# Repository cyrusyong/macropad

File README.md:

# macropad
Custom Macropad consisting of four keys

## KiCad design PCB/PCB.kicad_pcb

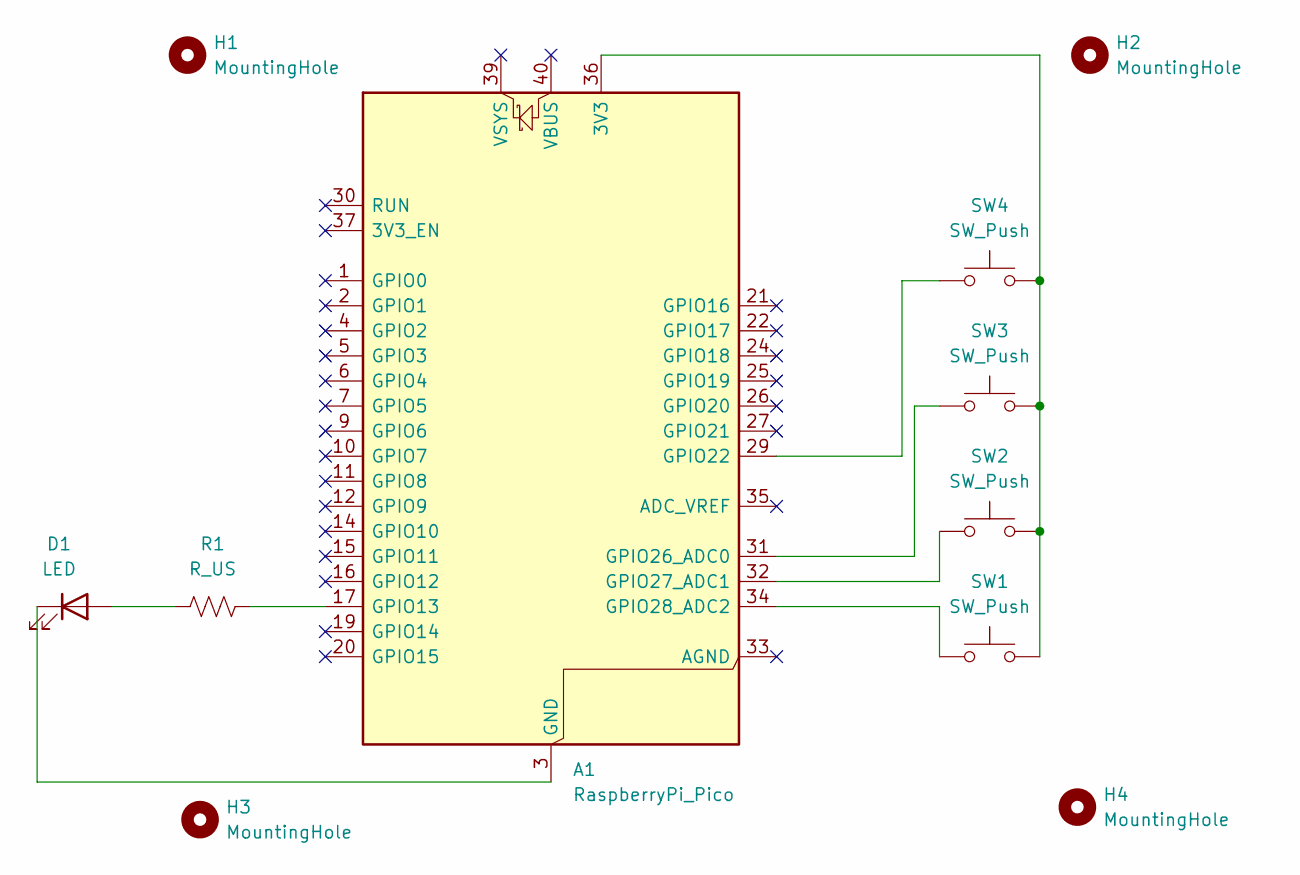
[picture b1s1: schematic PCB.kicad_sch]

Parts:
A1: RaspberryPi_Pico; RaspberryPi_Pico_Common_Unspecified
D1: LED; LED_1210_3225Metric_Pad1.42x2.65mm_HandSolder
H1, H2, H3, H4: MountingHole; MountingHole_2.2mm_M2
R1: R_US; R_0805_2012Metric_Pad1.20x1.40mm_HandSolder
SW1, SW2, SW3, SW4: SW_Push; SW_Cherry_MX_1.00u_PCB

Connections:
unnamed: A1.36 (3V3), SW1.2, SW2.2, SW3.2, SW4.2
unnamed: A1.17 (GPIO13), R1.2
unnamed: A1.29 (GPIO22), SW4.1
unnamed: A1.31 (GPIO26_ADC0), SW3.1
unnamed: A1.32 (GPIO27_ADC1), SW2.1
unnamed: A1.34 (GPIO28_ADC2), SW1.1
unnamed: D1.2 (A), R1.1
unnamed: A1.3 (GND), A1.8 (GND), A1.13 (GND), A1.18 (GND), A1.23 (GND), A1.28 (GND), A1.38 (GND), D1.1 (K)

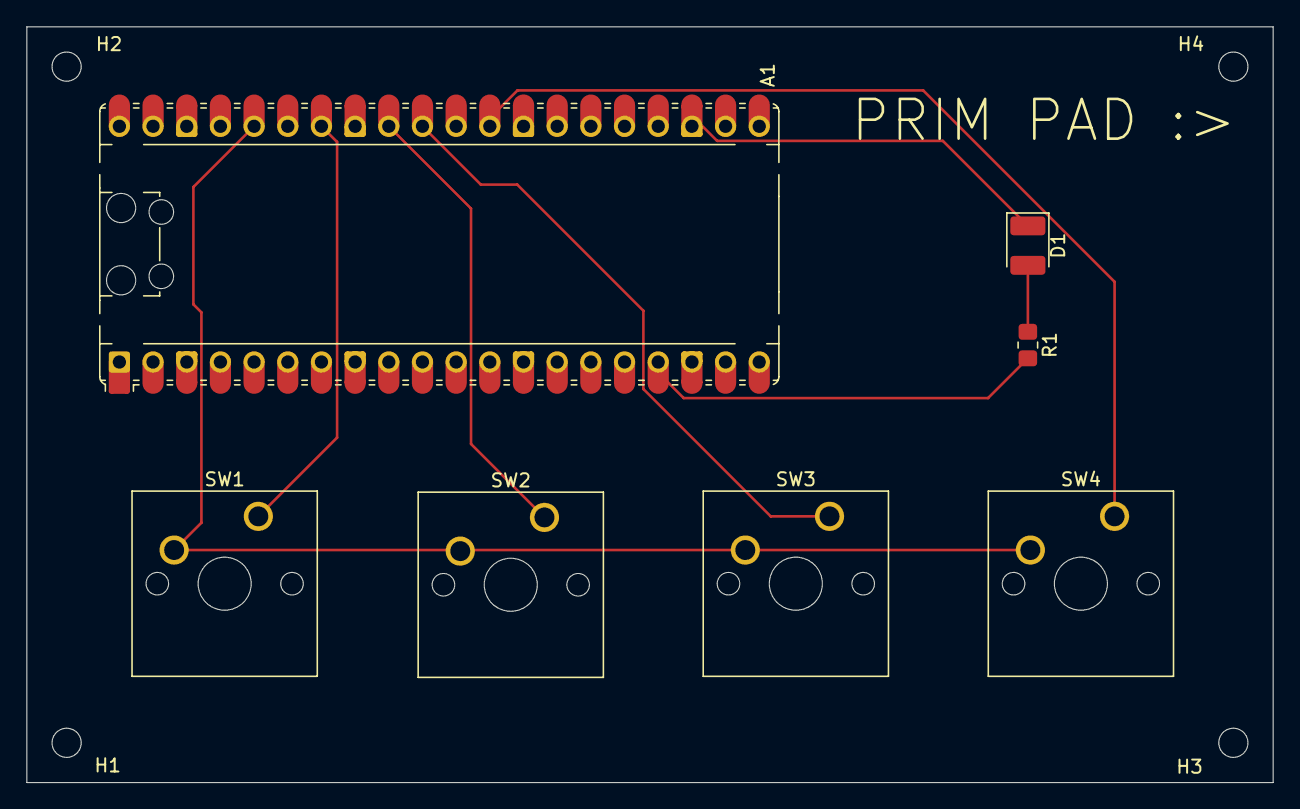
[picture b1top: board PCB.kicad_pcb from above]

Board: 2 copper layers, 94.0 x 57.0 mm, 11 parts (0 on the bottom side), 8 nets.

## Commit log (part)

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2026-06-16 test circuit with LEDs
2026-06-16 created tinyUSB configuration files
2026-06-16 updated ignore files
2026-06-16 create seperate files to store macro functions
2026-06-16 autoclicker sw1 complete
2026-06-17 button debouncer for sw1, basic implementation for sw2
2026-06-17 sw2 functionality completed, need testing
2026-06-17 added sw4 shutdown function, need testing for all
2026-06-18 change function to use win + number
2026-06-18 add PCB files
2026-06-18 reverted back to start menu search for SW3
2026-06-18 added '/' as a fix to SW4 functionality
2026-06-18 change type string gap to 20ms
